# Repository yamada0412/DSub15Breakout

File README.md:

# DSub15Breakout
DSub15Breakout

Ref:https://yamakashi.tech/?p=50

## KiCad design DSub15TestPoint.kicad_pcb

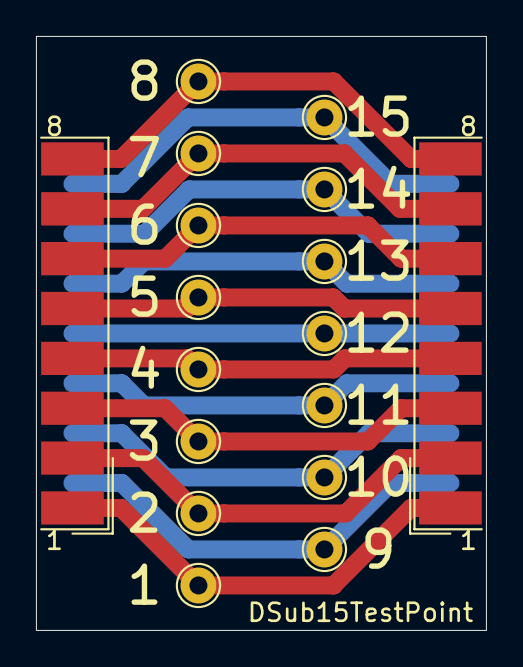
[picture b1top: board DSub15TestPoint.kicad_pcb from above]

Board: 2 copper layers, 25.0 x 33.0 mm, 17 parts (0 on the bottom side), 15 nets.

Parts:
1, 2, 3, 4, 5, 6, 7, 8, 9, 10, 11, 12, 13, 14, 15: TestPoint; TestPoint_THTPad_D2.0mm_Drill1.0mm
J1: DB15_Female; DSUB-15_Female_EdgeMount_P2.77mm
J2: DB15_Male; DSUB-15_Male_EdgeMount_P2.77mm

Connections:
P1: 1.1, J1.1, J2.1
P2: 2.1, J1.2, J2.2
P3: 3.1, J1.3, J2.3
P4: 4.1, J1.4, J2.4
P5: 5.1, J1.5, J2.5
P6: 6.1, J1.6, J2.6
P7: 7.1, J1.7, J2.7
P8: 8.1, J1.8, J2.8
P9: 9.1, J1.9, J2.9
P10: 10.1, J1.10, J2.10
P11: 11.1, J1.11, J2.11
P12: 12.1, J1.12, J2.12
P13: 13.1, J1.13, J2.13
P14: 14.1, J1.14, J2.14
P15: 15.1, J1.15, J2.15

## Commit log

2021-06-13 initial
    initial
